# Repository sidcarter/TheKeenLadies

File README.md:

# Acheron TKL-SM-S-ATM32U4-MX-TH-WI (Codename "TheKeenLadies")

See [this page](https://gondolindrim.github.io/AcheronDocs/keenladies/intro.html) for the TheKeenLadies documentation.

## Supported layouts

Click [this link](http://www.keyboard-layout-editor.com/#/gists/6fcb43072b2efaa6a5129e3db566da86) for the KLE file for the TheKeenLadies PCB.

## Renders

Click at the images to zoom in.

Renders generated by the [tracespace.io](https://tracespace.io/view/) site.

## Copyright notice

This project is released under the Acheron Open-Hardware License V1.1. For the license, please refer to the LICENCE.md file.

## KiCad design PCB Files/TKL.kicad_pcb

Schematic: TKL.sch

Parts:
C1, C2, C3, C4, C5, C6, C7, C8, C9, C10, C11, C12, C13, C14, C15, C16, C17, C18, C19, C20, C21, C22, C23, C24, C25, C26, C27, C28, C29, C30, C31, C32, C33, C34, C35, C36, C37, C38, C39, C40, C41, C42, C43, C44, C45, C46, C47, C48, C49, C50, C51, C52, C53, C54, C55, C56, C57, C58, C59, C60, C61, C62, C63, C64, C102, C105: 100nF; C_0805_2012Metric
CB1: 1uF; C_0402_1005Metric
CB2, CB3, CB4, CB5, CB6: 100nF; C_0402_1005Metric
CF1: 1u; C_0805_2012Metric_Pad1.15x1.40mm_HandSolder
CRST1: 100nF; C_0402_1005Metric
CSH1: 100nF; C_0805_2012Metric_Pad1.15x1.40mm_HandSolder
CU1: 1uF; C_0402_1005Metric
CUSB1: 100nF; C_0402_1005Metric
CX1, CX2: 8.2pF; C_0402_1005Metric
D1, D2, D3, D4, D5, D6, D7, D8, D9, D10, D11, D12, D13, D14, D15, D16, D17, D18, D19, D20, D21, D22, D23, D24, D25, D26, D27, D28, D29, D30, D31, D32, D33, D34, D35, D36, D37, D38, D39, D40, D41, D42, D43, D44, D45, D46, D47, D48, D49, D50, D51, D52, D53, D54, D55, D56, D57, D58, D59, D60, D61, D62, D63, D64, D65, D66, D67, D68, D69, D70, D71, D72, D73, D74, D75, D76, D77, D78, D79, D80, D81, D82, D83, D84, D85, D86, D87, D88, D89, D90: 1N4148; D_SOD-123
DF1: RB060M-60TR; D_SOD-123
F1: Polyfuse; Fuse_1206_3216Metric
G1: TKL Logo; TKL_Logo_11x18mm_Plated
G2: Acheron Short Logo Plated; acheronShort_15.2x21mm_Plated
G3: Warning sign; warning_sign_3.6x3.2mm
J1: USB_C; TYPE-C-31-M-12
L1, L2, L3, L4, L5, L6, L7, L8, L9, L10, L11, L12, L13, L14, L15, L16, L17, L18, L19, L20, L21, L22, L23, L24, L25, L26, L27, L28, L29, L30, L31, L32, L33, L34, L35, L36, L37, L38, L39, L40, L41, L42, L43, L44, L45, L46, L47, L48, L49, L50, L51, L52, L53, L54, L55, L56, L57, L58, L59, L60, L61, L62, L63, L64, L102, L105: LED_BGRA; LED_RGB_SMD_6028_2.8x3.5mm_Round
R1, R2, R3, R4, R5, R6, R7, R8, R9, R10, R11, R12, R13, R14, R15, R16, R17, R18, R19, R20, R21, R22, R23, R24, R25, R26, R27, R28, R29, R30, R31, R32, R33, R34, R35, R36, R37, R38, R39, R40, R41, R42, R43, R44, R45, R46, R47, R48, R49, R50, R51, R52, R53, R54, R55, R56, R57, R58, R59, R60, R61, R62, R63, R64, R102, R105: 100R; R_0805_2012Metric
RCC1: 5.1k; R_SMD_1026
RD1, RD2, RD3, RD4, RD5, RD6, RD7, RD8, RD9, RD10, RD11, RD12, RD13, RD14, RD15, RD16, RD18, RD19, RD20, RD21, RD22, RD23, RD24, RD25, RD26, RD27, RD28, RD29, RD30, RD31, RD32, RD33, RD34, RD35, RD36, RD37, RD38, RD39, RD40, RD41, RD42, RD43, RD44, RD45, RD46, RD47, RD48, RD49, RD50, RD51, RD52, RD54, RD55, RD56, RD57, RD58, RD59, RD60, RD61, RD62, RD63, RD64, RD102, RD105: 33R; R_0805_2012Metric
RDM1: 22; R_0805_2012Metric
RDP1: 22; R_0805_2012Metric
RDR1, RDR2: 33R; R_0805_2012Metric
RF1: 10k; R_SMD_1026
RHWB1: 1k; R_SMD_1026
RRST1: 4.7k; R_0805_2012Metric
RRST2: 330R; R_0805_2012Metric
RSH1: 1M; R_SMD_1026
SW1: ESC; MX100
SW2: F1; MX100
SW3: F2; MX100
SW4: F3; MX100
SW5: F4; MX100
SW6: F5; MX100
SW7: F6; MX100
SW8: F7; MX100
SW9: F8; MX100
SW10: F9; MX100
SW11: F10; MX100
SW12: F11; MX100
SW13: F12; MX100
SW14: PRTSC; MX100
SW15: SCRLCK; MX100
SW16: PAUSE; MX100
SW17: GRV; MX100
SW18: 1; MX100
SW19: 2; MX100
SW20: 3; MX100
SW21: 4; MX100
SW22: 5; MX100
SW23: 6; MX100
SW24: 7; MX100
SW25: 8; MX100
SW26: 9; MX100
SW27: 0; MX100
SW28: HIFEN; MX100
SW29: PLUS; MX100
SW30: BCKSLSH; MX100
SW31, SW49: DEL; MX100
SW32: INS; MX100
SW33: HOME; MX100
SW34: PGUP; MX100
SW35: TAB; MX150
SW36: Q; MX100
SW37: W; MX100
SW38: E; MX100
SW39: R; MX100
SW40: T; MX100
SW41: Y; MX100
SW42: U; MX100
SW43: I; MX100
SW44: O; MX100
SW45: P; MX100
SW46: LBRACES; MX100
SW47: RBRACES; MX100
SW48: BKSP_150; MX150
SW50: END; MX100
SW51: PGDN; MX100
SW52: CAPS; MX175
SW53: A; MX100
SW54: S; MX100
SW55: D; MX100
SW56: F; MX100
SW57: G; MX100
SW58: H; MX100
SW59: J; MX100
SW60: K; MX100
SW61: L; MX100
SW62: :; MX100
SW63: QUOTE; MX100
SW64: ENTER; MX225
SW65: LSHFT; MX225
SW66: Z; MX100
SW67: X; MX100
SW68: C; MX100
SW69: V; MX100
SW70: B; MX100
SW71: N; MX100
SW72: M; MX100
SW73: <,; MX100
SW74: .>; MX100
SW75: /; MX100
SW76: RSHFT_275; MX275
SW77: UP; MX100
SW78: LCTRL_B1; MX125
SW79: LGUI_B1; MX125
SW80: LALT_B1; MX125
SW81: SPACE_B1; MX625R
SW82: RALT_B1; MX125
SW83: RGUI_B1; MX125
SW84: MENU_R1; MX125
SW85: RCTRL_R1; MX125
SW86: LEFT; MX100
SW87: DOWN; MX100
SW88: RIGHT; MX100
SW89: LCTRL_B2; MX150
SW90: LGUI_B2; MX100
SW91: LALT_B3; MX100
SW92: LALT_B2; MX150
SW93: LGUI_B3; MX125
SW94: LSPC_R3; MX225R
SW95: SPACE_B2; MX700R
SW96: RSPC_B3; MX275R
SW97: RGUI_R3; MX125
SW98: RALT_B2; MX150
SW99: RALT_R3; MX100
SW100: RGUI_R2; MX100
SW101: RCTRL_R2; MX150
SW102: STEPPED_CAPS; MX125
SW103: RSHFT_175; MX175
SW104: Fn; MX100
SW105: BKSP_2U; MX200
SW_RST1: SW_Push; smdPushBtn
U1, U2, U3, U4, U5, U6, U7, U8, U9, U10, U11, U12, U13, U14, U15, U16, U17, U18, U19, U20, U21, U22, U23, U24, U25, U26, U27, U28, U29, U30, U31, U32, U33, U34, U35, U36, U37, U38, U39, U40, U41, U42, U43, U44, U45, U46, U47, U48, U49, U50, U51, U52, U53, U54, U55, U56, U57, U58, U59, U60, U61, U62, U63, U64, U102, U105: WS2811M; MSOP-8-1EP_3x3mm_P0.65mm_EP1.68x1.88mm
U200: ATMEGA32U4; QFN-44-1EP_7x7mm_P0.5mm_EP5.2x5.2mm
U201: USBLC6-2SC6; SOT-23-6
X1: 16MHz; Crystal_SMD_2016-4Pin_2.0x1.6mm

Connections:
5V: CB1.2, CB2.1, CB3.2, CB4.2, CB5.1, CB6.1, CF1.2, DF1.1 (K), F1.1, L1.4 (A), L2.4 (A), L3.4 (A), L4.4 (A), L5.4 (A), L6.4 (A), L7.4 (A), L8.4 (A), L9.4 (A), L10.4 (A), L11.4 (A), L12.4 (A), L13.4 (A), L14.4 (A), L15.4 (A), L16.4 (A), L17.4 (A), L18.4 (A), L19.4 (A), L20.4 (A), L21.4 (A), L22.4 (A), L23.4 (A), L24.4 (A), L25.4 (A), L26.4 (A), L27.4 (A), L28.4 (A), L29.4 (A), L30.4 (A), L31.4 (A), L32.4 (A), L33.4 (A), L34.4 (A), L35.4 (A), L36.4 (A), L37.4 (A), L38.4 (A), L39.4 (A), L40.4 (A), L41.4 (A), L42.4 (A), L43.4 (A), L44.4 (A), L45.4 (A), L46.4 (A), L47.4 (A), L48.4 (A), L49.4 (A), L50.4 (A), L51.4 (A), L52.4 (A), L53.4 (A), L54.4 (A), L55.4 (A), L56.4 (A), L57.4 (A), L58.4 (A), L59.4 (A), L60.4 (A), L61.4 (A), L62.4 (A), L63.4 (A), L64.4 (A), L102.4 (A), L105.4 (A), R1.1, R2.1, R3.1, R4.1, R5.1, R6.1, R7.1, R8.1, R9.1, R10.1, R11.1, R12.1, R13.1, R14.1, R15.1, R16.1, R17.1, R18.1, R19.1, R20.1, R21.1, R22.1, R23.1, R24.1, R25.1, R26.1, R27.1, R28.1, R29.1, R30.1, R31.1, R32.1, R33.1, R34.1, R35.1, R36.1, R37.1, R38.1, R39.1, R40.1, R41.1, R42.1, R43.1, R44.1, R45.1, R46.1, R47.1, R48.1, R49.1, R50.1, R51.1, R52.1, R53.1, R54.1, R55.1, R56.1, R57.1, R58.1, R59.1, R60.1, R61.1, R62.1, R63.1, R64.1, R102.1, R105.1, RF1.2, RRST1.2, U200.2 (UVCC), U200.7 (VBUS), U200.14 (VCC), U200.24 (AVCC), U200.35 (GND), U200.42 (AREF), U200.44 (AVCC)
/RST: CRST1.2, RRST1.1, RRST2.2, U200.13 (~RESET~)
/SHIELD: CSH1.1, J1.S (SHIELD), RSH1.2
/XTAL1: CX2.1, U200.17 (XTAL1), X1.1
/XTAL2: CX1.1, U200.16 (XTAL2), X1.3
Col1: SW1.1 (Col), SW17.1 (Col), SW35.1 (Col), SW52.1 (Col), SW65.1 (Col), SW78.1 (Col), SW89.1 (Col), SW102.1 (Col)
Col2: SW18.1 (Col), SW36.1 (Col), SW53.1 (Col), SW66.1 (Col), SW79.1 (Col), SW90.1 (Col), SW91.1 (Col)
Col3: SW2.1 (Col), SW19.1 (Col), SW37.1 (Col), SW54.1 (Col), SW67.1 (Col), SW80.1 (Col), SW92.1 (Col), SW93.1 (Col)
Col4: SW3.1 (Col), SW20.1 (Col), SW38.1 (Col), SW55.1 (Col), SW68.1 (Col)
Col5: SW4.1 (Col), SW21.1 (Col), SW39.1 (Col), SW56.1 (Col), SW69.1 (Col), SW94.1 (Col)
Col6: SW5.1 (Col), SW22.1 (Col), SW40.1 (Col), SW57.1 (Col), SW70.1 (Col)
Col7: SW23.1 (Col), SW41.1 (Col), SW58.1 (Col), SW71.1 (Col), SW81.1 (Col), SW95.1 (Col), SW96.1 (Col)
Col8: SW6.1 (Col), SW24.1 (Col), SW42.1 (Col), SW59.1 (Col), SW72.1 (Col)
Col9: SW7.1 (Col), SW25.1 (Col), SW43.1 (Col), SW60.1 (Col), SW73.1 (Col)
Col10: SW8.1 (Col), SW26.1 (Col), SW44.1 (Col), SW61.1 (Col), SW74.1 (Col), SW82.1 (Col), SW97.1 (Col)
Col11: SW9.1 (Col), SW27.1 (Col), SW45.1 (Col), SW62.1 (Col), SW75.1 (Col), SW83.1 (Col), SW98.1 (Col), SW99.1 (Col)
Col12: SW10.1 (Col), SW28.1 (Col), SW46.1 (Col)
Col13: SW11.1 (Col), SW29.1 (Col), SW47.1 (Col), SW63.1 (Col), SW76.1 (Col), SW84.1 (Col), SW100.1 (Col), SW103.1 (Col)
Col14: SW12.1 (Col), SW30.1 (Col)
Col15: SW13.1 (Col), SW31.1 (Col), SW48.1 (Col), SW64.1 (Col), SW85.1 (Col), SW101.1 (Col), SW104.1 (Col), SW105.1 (Col)
Col16: SW14.1 (Col), SW32.1 (Col), SW49.1 (Col), SW86.1 (Col)
Col17: SW15.1 (Col), SW33.1 (Col), SW50.1 (Col), SW77.1 (Col), SW87.1 (Col)
Col18: SW16.1 (Col), SW34.1 (Col), SW51.1 (Col), SW88.1 (Col)
DBusN: J1.A7 (D-), J1.B7 (D-), U201.1 (IO1)
DBusP: J1.A6 (D+), J1.B6 (D+), U201.3 (IO2)
DN: RDM1.2, U200.3 (D-)
DP: RDP1.1, U200.4 (D+)
GND: C1.2, C2.2, C3.2, C4.2, C5.2, C6.2, C7.2, C8.2, C9.2, C10.2, C11.2, C12.2, C13.2, C14.2, C15.2, C16.2, C17.2, C18.2, C19.2, C20.2, C21.2, C22.2, C23.2, C24.2, C25.2, C26.2, C27.2, C28.2, C29.2, C30.2, C31.2, C32.2, C33.2, C34.2, C35.2, C36.2, C37.2, C38.2, C39.2, C40.2, C41.2, C42.2, C43.2, C44.2, C45.2, C46.2, C47.2, C48.2, C49.2, C50.2, C51.2, C52.2, C53.2, C54.2, C55.2, C56.2, C57.2, C58.2, C59.2, C60.2, C61.2, C62.2, C63.2, C64.2, C102.2, C105.2, CB1.1, CB2.2, CB3.1, CB4.1, CB5.2, CB6.2, CF1.1, CRST1.1, CSH1.2, CU1.2, CUSB1.2, CX1.2, CX2.2, DF1.2 (A), J1.A1 (GND), J1.B1 (GND), RCC1.2, RF1.1, RHWB1.1, RSH1.1, SW_RST1.1, U1.4 (GND), U1.9 (GND), U2.4 (GND), U2.9 (GND), U3.4 (GND), U3.9 (GND), U4.4 (GND), U4.9 (GND), U5.4 (GND), U5.9 (GND), U6.4 (GND), U6.9 (GND), U7.4 (GND), U7.9 (GND), U8.4 (GND), U8.9 (GND), U9.4 (GND), U9.9 (GND), U10.4 (GND), U10.9 (GND), U11.4 (GND), U11.9 (GND), U12.4 (GND), U12.9 (GND), U13.4 (GND), U13.9 (GND), U14.4 (GND), U14.9 (GND), U15.4 (GND), U15.9 (GND), U16.4 (GND), U16.9 (GND), U17.4 (GND), U17.9 (GND), U18.4 (GND), U18.9 (GND), U19.4 (GND), U19.9 (GND), U20.4 (GND), U20.9 (GND), U21.4 (GND), U21.9 (GND), U22.4 (GND), U22.9 (GND), U23.4 (GND), U23.9 (GND), U24.4 (GND), U24.9 (GND), U25.4 (GND), U25.9 (GND), U26.4 (GND), U26.9 (GND), U27.4 (GND), U27.9 (GND), U28.4 (GND), U28.9 (GND), U29.4 (GND), U29.9 (GND), U30.4 (GND), U30.9 (GND), U31.4 (GND), U31.9 (GND), U32.4 (GND), U32.9 (GND), U33.4 (GND), U33.9 (GND), U34.4 (GND), U34.9 (GND), U35.4 (GND), U35.9 (GND), U36.4 (GND), U36.9 (GND), U37.4 (GND), U37.9 (GND), U38.4 (GND), U38.9 (GND), U39.4 (GND), U39.9 (GND), U40.4 (GND), U40.9 (GND), U41.4 (GND), U41.9 (GND), U42.4 (GND), U42.9 (GND), U43.4 (GND), U43.9 (GND), U44.4 (GND), U44.9 (GND), U45.4 (GND), U45.9 (GND), U46.4 (GND), U46.9 (GND), U47.4 (GND), U47.9 (GND), U48.4 (GND), U48.9 (GND), U49.4 (GND), U49.9 (GND), U50.4 (GND), U50.9 (GND), U51.4 (GND), U51.9 (GND), U52.4 (GND), U52.9 (GND), U53.4 (GND), U53.9 (GND), U54.4 (GND), U54.9 (GND), U55.4 (GND), U55.9 (GND), U56.4 (GND), U56.9 (GND), U57.4 (GND), U57.9 (GND), U58.4 (GND), U58.9 (GND), U59.4 (GND), U59.9 (GND), U60.4 (GND), U60.9 (GND), U61.4 (GND), U61.9 (GND), U62.4 (GND), U62.9 (GND), U63.4 (GND), U63.9 (GND), U64.4 (GND), U64.9 (GND), U102.4 (GND), U102.9 (GND), U105.4 (GND), U105.9 (GND), U200.5 (UGND), U200.15 (GND), U200.23 (GND), U200.34 (VCC), U200.43 (GND), U201.2 (GND), X1.2, X1.4
L1: D78.2 (A), SW78.2 (Row), SW89.2 (Row)
L2: D79.2 (A), SW79.2 (Row), SW90.2 (Row), SW91.2 (Row)
L3: D80.2 (A), SW80.2 (Row), SW92.2 (Row), SW93.2 (Row)
L4: D81.2 (A), SW81.2 (Row), SW95.2 (Row), SW96.2 (Row)
L5: D82.2 (A), SW82.2 (Row), SW97.2 (Row)
L6: D83.2 (A), SW83.2 (Row), SW98.2 (Row), SW99.2 (Row)
L7: D84.2 (A), SW84.2 (Row), SW100.2 (Row)
L8: D85.2 (A), SW85.2 (Row), SW101.2 (Row)
unnamed: C1.1, R1.2, U1.8 (VDD)
unnamed: C2.1, R2.2, U2.8 (VDD)
unnamed: C3.1, R3.2, U3.8 (VDD)
unnamed: C4.1, R4.2, U4.8 (VDD)
unnamed: C5.1, R5.2, U5.8 (VDD)
unnamed: C6.1, R6.2, U6.8 (VDD)
unnamed: C7.1, R7.2, U7.8 (VDD)
unnamed: C8.1, R8.2, U8.8 (VDD)
unnamed: C9.1, R9.2, U9.8 (VDD)
unnamed: C10.1, R10.2, U10.8 (VDD)
unnamed: C11.1, R11.2, U11.8 (VDD)
unnamed: C12.1, R12.2, U12.8 (VDD)
unnamed: C13.1, R13.2, U13.8 (VDD)
unnamed: C14.1, R14.2, U14.8 (VDD)
unnamed: C15.1, R15.2, U15.8 (VDD)
unnamed: C16.1, R16.2, U16.8 (VDD)
unnamed: C17.1, R17.2, U17.8 (VDD)
unnamed: C18.1, R18.2, U18.8 (VDD)
unnamed: C19.1, R19.2, U19.8 (VDD)
unnamed: C20.1, R20.2, U20.8 (VDD)
unnamed: C21.1, R21.2, U21.8 (VDD)
unnamed: C22.1, R22.2, U22.8 (VDD)
unnamed: C23.1, R23.2, U23.8 (VDD)
unnamed: C24.1, R24.2, U24.8 (VDD)
unnamed: C25.1, R25.2, U25.8 (VDD)
unnamed: C26.1, R26.2, U26.8 (VDD)
unnamed: C27.1, R27.2, U27.8 (VDD)
unnamed: C28.1, R28.2, U28.8 (VDD)
unnamed: C29.1, R29.2, U29.8 (VDD)
unnamed: C30.1, R30.2, U30.8 (VDD)
unnamed: C31.1, R31.2, U31.8 (VDD)
unnamed: C32.1, R32.2, U32.8 (VDD)
unnamed: C33.1, R33.2, U33.8 (VDD)
unnamed: C34.1, R34.2, U34.8 (VDD)
unnamed: C35.1, R35.2, U35.8 (VDD)
unnamed: C36.1, R36.2, U36.8 (VDD)
unnamed: C37.1, R37.2, U37.8 (VDD)
unnamed: C38.1, R38.2, U38.8 (VDD)
unnamed: C39.1, R39.2, U39.8 (VDD)
unnamed: C40.1, R40.2, U40.8 (VDD)
unnamed: C41.1, R41.2, U41.8 (VDD)
unnamed: C42.1, R42.2, U42.8 (VDD)
unnamed: C43.1, R43.2, U43.8 (VDD)
unnamed: C44.1, R44.2, U44.8 (VDD)
unnamed: C45.1, R45.2, U45.8 (VDD)
unnamed: C46.1, R46.2, U46.8 (VDD)
unnamed: C47.1, R47.2, U47.8 (VDD)
unnamed: C48.1, R48.2, U48.8 (VDD)
unnamed: C49.1, R49.2, U49.8 (VDD)
unnamed: C50.1, R50.2, U50.8 (VDD)
unnamed: C51.1, R51.2, U51.8 (VDD)
unnamed: C52.1, R52.2, U52.8 (VDD)
unnamed: C53.1, R53.2, U53.8 (VDD)
unnamed: C54.1, R54.2, U54.8 (VDD)
unnamed: C55.1, R55.2, U55.8 (VDD)
unnamed: C56.1, R56.2, U56.8 (VDD)
unnamed: C57.1, R57.2, U57.8 (VDD)
unnamed: C58.1, R58.2, U58.8 (VDD)
unnamed: C59.1, R59.2, U59.8 (VDD)
unnamed: C60.1, R60.2, U60.8 (VDD)
unnamed: C61.1, R61.2, U61.8 (VDD)
unnamed: C62.1, R62.2, U62.8 (VDD)
unnamed: C63.1, R63.2, U63.8 (VDD)
unnamed: C64.1, R64.2, U64.8 (VDD)
unnamed: C102.1, R102.2, U102.8 (VDD)
unnamed: C105.1, R105.2, U105.8 (VDD)
unnamed: CU1.1, U200.6 (UCAP)
unnamed: D1.2 (A), SW1.2 (Row)
unnamed: D2.2 (A), SW2.2 (Row)
unnamed: D3.2 (A), SW3.2 (Row)
unnamed: D4.2 (A), SW4.2 (Row)
unnamed: D5.2 (A), SW5.2 (Row)
unnamed: D6.2 (A), SW6.2 (Row)
unnamed: D7.2 (A), SW7.2 (Row)
unnamed: D8.2 (A), SW8.2 (Row)
unnamed: D9.2 (A), SW9.2 (Row)
unnamed: D10.2 (A), SW10.2 (Row)
unnamed: D11.2 (A), SW11.2 (Row)
unnamed: D12.2 (A), SW12.2 (Row)
unnamed: D13.2 (A), SW13.2 (Row)
unnamed: D14.2 (A), SW14.2 (Row)
unnamed: D15.2 (A), SW15.2 (Row)
unnamed: D16.2 (A), SW16.2 (Row)
unnamed: D17.2 (A), SW17.2 (Row)
unnamed: D18.2 (A), SW18.2 (Row)
unnamed: D19.2 (A), SW19.2 (Row)
unnamed: D20.2 (A), SW20.2 (Row)
unnamed: D21.2 (A), SW21.2 (Row)
unnamed: D22.2 (A), SW22.2 (Row)
unnamed: D23.2 (A), SW23.2 (Row)
unnamed: D24.2 (A), SW24.2 (Row)
unnamed: D25.2 (A), SW25.2 (Row)
unnamed: D26.2 (A), SW26.2 (Row)
unnamed: D27.2 (A), SW27.2 (Row)
unnamed: D28.2 (A), SW28.2 (Row)
unnamed: D29.2 (A), SW29.2 (Row)
unnamed: D30.2 (A), SW30.2 (Row)
unnamed: D31.2 (A), SW31.2 (Row), SW105.2 (Row)
unnamed: D32.2 (A), SW32.2 (Row)
unnamed: D33.2 (A), SW33.2 (Row)
unnamed: D34.2 (A), SW34.2 (Row)
unnamed: D35.2 (A), SW35.2 (Row)
unnamed: D36.2 (A), SW36.2 (Row)
unnamed: D37.2 (A), SW37.2 (Row)
unnamed: D38.2 (A), SW38.2 (Row)
unnamed: D39.2 (A), SW39.2 (Row)
unnamed: D40.2 (A), SW40.2 (Row)
unnamed: D41.2 (A), SW41.2 (Row)
unnamed 144: D42.2 (A), SW42.2 (Row); also elsewhere on the board
unnamed: D43.2 (A), SW43.2 (Row)
unnamed: D44.2 (A), SW44.2 (Row)
unnamed: D45.2 (A), SW45.2 (Row)
unnamed: D46.2 (A), SW46.2 (Row)
unnamed: D47.2 (A), SW47.2 (Row)
unnamed: D48.2 (A), SW48.2 (Row)
unnamed: D49.2 (A), SW49.2 (Row)
unnamed: D50.2 (A), SW50.2 (Row)
unnamed: D51.2 (A), SW51.2 (Row)
unnamed: D52.2 (A), SW52.2 (Row), SW102.2 (Row)
unnamed: D53.2 (A), SW53.2 (Row)
unnamed: D54.2 (A), SW54.2 (Row)
unnamed: D55.2 (A), SW55.2 (Row)
unnamed: D56.2 (A), SW56.2 (Row)
unnamed: D57.2 (A), SW57.2 (Row)
unnamed: D58.2 (A), SW58.2 (Row)
unnamed: D59.2 (A), SW59.2 (Row)
unnamed: D60.2 (A), SW60.2 (Row)
unnamed: D61.2 (A), SW61.2 (Row)
unnamed: D62.2 (A), SW62.2 (Row)
unnamed: D63.2 (A), SW63.2 (Row)
unnamed: D64.2 (A), SW64.2 (Row)
unnamed: D65.2 (A), SW65.2 (Row)
unnamed: D66.2 (A), SW66.2 (Row)
unnamed: D67.2 (A), SW67.2 (Row)
unnamed: D68.2 (A), SW68.2 (Row)
unnamed: D69.2 (A), SW69.2 (Row)
unnamed: D70.2 (A), SW70.2 (Row)
unnamed: D71.2 (A), SW71.2 (Row)
unnamed: D72.2 (A), SW72.2 (Row)
unnamed: D73.2 (A), SW73.2 (Row)
unnamed: D74.2 (A), SW74.2 (Row)
unnamed: D75.2 (A), SW75.2 (Row)
unnamed: D76.2 (A), SW76.2 (Row), SW103.2 (Row)
unnamed: D77.2 (A), SW77.2 (Row)
unnamed: D86.2 (A), SW86.2 (Row)
unnamed: D87.2 (A), SW87.2 (Row)
unnamed: D88.2 (A), SW88.2 (Row)
unnamed: D89.2 (A), SW94.2 (Row)
unnamed: D90.2 (A), SW104.2 (Row)
unnamed: J1.A5 (CC1), J1.B5 (CC2), RCC1.1
unnamed: L1.1 (BK), U1.3 (OUTB)
unnamed: L1.2 (GK), U1.2 (OUTG)
unnamed: L1.3 (RK), U1.1 (OUTR)
unnamed: L2.1 (BK), U2.3 (OUTB)
unnamed: L2.2 (GK), U2.2 (OUTG)
unnamed: L2.3 (RK), U2.1 (OUTR)
unnamed: L3.1 (BK), U3.3 (OUTB)
unnamed: L3.2 (GK), U3.2 (OUTG)
unnamed: L3.3 (RK), U3.1 (OUTR)
unnamed: L4.1 (BK), U4.3 (OUTB)
unnamed: L4.2 (GK), U4.2 (OUTG)
unnamed: L4.3 (RK), U4.1 (OUTR)
unnamed: L5.1 (BK), U5.3 (OUTB)
unnamed: L5.2 (GK), U5.2 (OUTG)
unnamed: L5.3 (RK), U5.1 (OUTR)
unnamed: L6.1 (BK), U6.3 (OUTB)
unnamed: L6.2 (GK), U6.2 (OUTG)
unnamed: L6.3 (RK), U6.1 (OUTR)
unnamed: L7.1 (BK), U7.3 (OUTB)
unnamed: L7.2 (GK), U7.2 (OUTG)
unnamed: L7.3 (RK), U7.1 (OUTR)
unnamed: L8.1 (BK), U8.3 (OUTB)
unnamed: L8.2 (GK), U8.2 (OUTG)
unnamed: L8.3 (RK), U8.1 (OUTR)
unnamed: L9.1 (BK), U9.3 (OUTB)
unnamed: L9.2 (GK), U9.2 (OUTG)
unnamed: L9.3 (RK), U9.1 (OUTR)
unnamed: L10.1 (BK), U10.3 (OUTB)
unnamed: L10.2 (GK), U10.2 (OUTG)
unnamed: L10.3 (RK), U10.1 (OUTR)
unnamed: L11.1 (BK), U11.3 (OUTB)
unnamed: L11.2 (GK), U11.2 (OUTG)
unnamed: L11.3 (RK), U11.1 (OUTR)
unnamed: L12.1 (BK), U12.3 (OUTB)
unnamed: L12.2 (GK), U12.2 (OUTG)
unnamed: L12.3 (RK), U12.1 (OUTR)
unnamed: L13.1 (BK), U13.3 (OUTB)
unnamed: L13.2 (GK), U13.2 (OUTG)
unnamed: L13.3 (RK), U13.1 (OUTR)
unnamed: L14.1 (BK), U14.3 (OUTB)
unnamed: L14.2 (GK), U14.2 (OUTG)
unnamed: L14.3 (RK), U14.1 (OUTR)
unnamed: L15.1 (BK), U15.3 (OUTB)
unnamed: L15.2 (GK), U15.2 (OUTG)
unnamed: L15.3 (RK), U15.1 (OUTR)
unnamed: L16.1 (BK), U16.3 (OUTB)
unnamed: L16.2 (GK), U16.2 (OUTG)
unnamed: L16.3 (RK), U16.1 (OUTR)
unnamed: L17.1 (BK), U17.3 (OUTB)
unnamed: L17.2 (GK), U17.2 (OUTG)
unnamed: L17.3 (RK), U17.1 (OUTR)
unnamed: L18.1 (BK), U18.3 (OUTB)
unnamed: L18.2 (GK), U18.2 (OUTG)
unnamed: L18.3 (RK), U18.1 (OUTR)
unnamed: L19.1 (BK), U19.3 (OUTB)
unnamed: L19.2 (GK), U19.2 (OUTG)
unnamed: L19.3 (RK), U19.1 (OUTR)
unnamed: L20.1 (BK), U20.3 (OUTB)
unnamed: L20.2 (GK), U20.2 (OUTG)
unnamed: L20.3 (RK), U20.1 (OUTR)
unnamed: L21.1 (BK), U21.3 (OUTB)
unnamed: L21.2 (GK), U21.2 (OUTG)
unnamed: L21.3 (RK), U21.1 (OUTR)
unnamed: L22.1 (BK), U22.3 (OUTB)
unnamed: L22.2 (GK), U22.2 (OUTG)
unnamed: L22.3 (RK), U22.1 (OUTR)
unnamed: L23.1 (BK), U23.3 (OUTB)
unnamed: L23.2 (GK), U23.2 (OUTG)
unnamed: L23.3 (RK), U23.1 (OUTR)
unnamed: L24.1 (BK), U24.3 (OUTB)
unnamed: L24.2 (GK), U24.2 (OUTG)
unnamed: L24.3 (RK), U24.1 (OUTR)
unnamed: L25.1 (BK), U25.3 (OUTB)
unnamed: L25.2 (GK), U25.2 (OUTG)
unnamed: L25.3 (RK), U25.1 (OUTR)
unnamed: L26.1 (BK), U26.3 (OUTB)
unnamed: L26.2 (GK), U26.2 (OUTG)
unnamed: L26.3 (RK), U26.1 (OUTR)
unnamed: L27.1 (BK), U27.3 (OUTB)
unnamed: L27.2 (GK), U27.2 (OUTG)
unnamed: L27.3 (RK), U27.1 (OUTR)
unnamed: L28.1 (BK), U28.3 (OUTB)
unnamed: L28.2 (GK), U28.2 (OUTG)
unnamed: L28.3 (RK), U28.1 (OUTR)
unnamed: L29.1 (BK), U29.3 (OUTB)
unnamed: L29.2 (GK), U29.2 (OUTG)
unnamed: L29.3 (RK), U29.1 (OUTR)
unnamed: L30.1 (BK), U30.3 (OUTB)
unnamed: L30.2 (GK), U30.2 (OUTG)
unnamed: L30.3 (RK), U30.1 (OUTR)
unnamed: L31.1 (BK), U31.3 (OUTB)
unnamed: L31.2 (GK), U31.2 (OUTG)
unnamed: L31.3 (RK), U31.1 (OUTR)
unnamed: L32.1 (BK), U32.3 (OUTB)
unnamed: L32.2 (GK), U32.2 (OUTG)
unnamed: L32.3 (RK), U32.1 (OUTR)
unnamed: L33.1 (BK), U33.3 (OUTB)
unnamed: L33.2 (GK), U33.2 (OUTG)
unnamed: L33.3 (RK), U33.1 (OUTR)
unnamed: L34.1 (BK), U34.3 (OUTB)
unnamed: L34.2 (GK), U34.2 (OUTG)
unnamed: L34.3 (RK), U34.1 (OUTR)
unnamed: L35.1 (BK), U35.3 (OUTB)
unnamed: L35.2 (GK), U35.2 (OUTG)
unnamed: L35.3 (RK), U35.1 (OUTR)
unnamed: L36.1 (BK), U36.3 (OUTB)
unnamed: L36.2 (GK), U36.2 (OUTG)
unnamed: L36.3 (RK), U36.1 (OUTR)
unnamed: L37.1 (BK), U37.3 (OUTB)
unnamed: L37.2 (GK), U37.2 (OUTG)
unnamed: L37.3 (RK), U37.1 (OUTR)
unnamed: L38.1 (BK), U38.3 (OUTB)
unnamed: L38.2 (GK), U38.2 (OUTG)
unnamed: L38.3 (RK), U38.1 (OUTR)
unnamed: L39.1 (BK), U39.3 (OUTB)
unnamed: L39.2 (GK), U39.2 (OUTG)
unnamed: L39.3 (RK), U39.1 (OUTR)
unnamed: L40.1 (BK), U40.3 (OUTB)
unnamed: L40.2 (GK), U40.2 (OUTG)
unnamed: L40.3 (RK), U40.1 (OUTR)
unnamed: L41.1 (BK), U41.3 (OUTB)
unnamed: L41.2 (GK), U41.2 (OUTG)
unnamed: L41.3 (RK), U41.1 (OUTR)
unnamed: L42.1 (BK), U42.3 (OUTB)
unnamed: L42.2 (GK), U42.2 (OUTG)
unnamed: L42.3 (RK), U42.1 (OUTR)
unnamed: L43.1 (BK), U43.3 (OUTB)
unnamed: L43.2 (GK), U43.2 (OUTG)
unnamed: L43.3 (RK), U43.1 (OUTR)
unnamed: L44.1 (BK), U44.3 (OUTB)
unnamed: L44.2 (GK), U44.2 (OUTG)
unnamed: L44.3 (RK), U44.1 (OUTR)
unnamed: L45.1 (BK), U45.3 (OUTB)
unnamed: L45.2 (GK), U45.2 (OUTG)
unnamed: L45.3 (RK), U45.1 (OUTR)
unnamed: L46.1 (BK), U46.3 (OUTB)
unnamed: L46.2 (GK), U46.2 (OUTG)
unnamed: L46.3 (RK), U46.1 (OUTR)
unnamed: L47.1 (BK), U47.3 (OUTB)
unnamed: L47.2 (GK), U47.2 (OUTG)
unnamed: L47.3 (RK), U47.1 (OUTR)
unnamed: L48.1 (BK), U48.3 (OUTB)
unnamed: L48.2 (GK), U48.2 (OUTG)
unnamed: L48.3 (RK), U48.1 (OUTR)
unnamed: L49.1 (BK), U49.3 (OUTB)
unnamed: L49.2 (GK), U49.2 (OUTG)
unnamed: L49.3 (RK), U49.1 (OUTR)
unnamed: L50.1 (BK), U50.3 (OUTB)
unnamed: L50.2 (GK), U50.2 (OUTG)
unnamed: L50.3 (RK), U50.1 (OUTR)
unnamed: L51.1 (BK), U51.3 (OUTB)
unnamed: L51.2 (GK), U51.2 (OUTG)
unnamed: L51.3 (RK), U51.1 (OUTR)
unnamed: L52.1 (BK), U52.3 (OUTB)
unnamed: L52.2 (GK), U52.2 (OUTG)
unnamed: L52.3 (RK), U52.1 (OUTR)
unnamed: L53.1 (BK), U53.3 (OUTB)
unnamed: L53.2 (GK), U53.2 (OUTG)
unnamed: L53.3 (RK), U53.1 (OUTR)
unnamed: L54.1 (BK), U54.3 (OUTB)
unnamed: L54.2 (GK), U54.2 (OUTG)
unnamed: L54.3 (RK), U54.1 (OUTR)
unnamed: L55.1 (BK), U55.3 (OUTB)
unnamed: L55.2 (GK), U55.2 (OUTG)
unnamed: L55.3 (RK), U55.1 (OUTR)
unnamed: L56.1 (BK), U56.3 (OUTB)
unnamed: L56.2 (GK), U56.2 (OUTG)
unnamed: L56.3 (RK), U56.1 (OUTR)
unnamed: L57.1 (BK), U57.3 (OUTB)
unnamed: L57.2 (GK), U57.2 (OUTG)
unnamed: L57.3 (RK), U57.1 (OUTR)
unnamed: L58.1 (BK), U58.3 (OUTB)
unnamed: L58.2 (GK), U58.2 (OUTG)
unnamed: L58.3 (RK), U58.1 (OUTR)
unnamed: L59.1 (BK), U59.3 (OUTB)
unnamed: L59.2 (GK), U59.2 (OUTG)
unnamed: L59.3 (RK), U59.1 (OUTR)
unnamed: L60.1 (BK), U60.3 (OUTB)
unnamed: L60.2 (GK), U60.2 (OUTG)
unnamed: L60.3 (RK), U60.1 (OUTR)
unnamed: L61.1 (BK), U61.3 (OUTB)
unnamed: L61.2 (GK), U61.2 (OUTG)
unnamed: L61.3 (RK), U61.1 (OUTR)
unnamed: L62.1 (BK), U62.3 (OUTB)
unnamed: L62.2 (GK), U62.2 (OUTG)
unnamed: L62.3 (RK), U62.1 (OUTR)
unnamed: L63.1 (BK), U63.3 (OUTB)
unnamed: L63.2 (GK), U63.2 (OUTG)
unnamed: L63.3 (RK), U63.1 (OUTR)
unnamed: L64.1 (BK), U64.3 (OUTB)
unnamed: L64.2 (GK), U64.2 (OUTG)
unnamed: L64.3 (RK), U64.1 (OUTR)
unnamed: L102.1 (BK), U102.3 (OUTB)
unnamed: L102.2 (GK), U102.2 (OUTG)
unnamed: L102.3 (RK), U102.1 (OUTR)
unnamed: L105.1 (BK), U105.3 (OUTB)
unnamed: L105.2 (GK), U105.2 (OUTG)
unnamed: L105.3 (RK), U105.1 (OUTR)
unnamed: RD1.1, U1.6 (DIN)
unnamed: RD2.1, U2.6 (DIN)
unnamed: RD2.2, U1.5 (DO)
unnamed: RD3.1, U3.6 (DIN)
unnamed: RD3.2, U2.5 (DO)
unnamed: RD4.1, U4.6 (DIN)
unnamed: RD4.2, U3.5 (DO)
unnamed: RD5.1, U5.6 (DIN)
unnamed: RD5.2, U4.5 (DO)
unnamed: RD6.1, U6.6 (DIN)
unnamed: RD6.2, U5.5 (DO)
unnamed: RD7.1, U7.6 (DIN)
unnamed: RD7.2, U6.5 (DO)
unnamed: RD8.1, U8.6 (DIN)
unnamed: RD8.2, U7.5 (DO)
unnamed: RD9.1, U9.6 (DIN)
unnamed: RD9.2, U8.5 (DO)
unnamed: RD10.1, U10.6 (DIN)
unnamed: RD10.2, U9.5 (DO)
unnamed: RD11.1, U11.6 (DIN)
unnamed: RD11.2, U10.5 (DO)
unnamed: RD12.1, U12.6 (DIN)
unnamed: RD12.2, U11.5 (DO)
unnamed: RD13.1, U13.6 (DIN)
unnamed: RD13.2, U12.5 (DO)
unnamed: RD14.1, U14.6 (DIN)
unnamed: RD14.2, U13.5 (DO)
unnamed: RD15.1, U15.6 (DIN)
unnamed: RD15.2, U14.5 (DO)
unnamed: RD16.1, U16.6 (DIN)
unnamed: RD16.2, U15.5 (DO)
unnamed: RD18.1, U17.6 (DIN)
unnamed: RD18.2, U18.5 (DO)
unnamed: RD19.1, U18.6 (DIN)
unnamed: RD19.2, U19.5 (DO)
unnamed: RD20.1, U19.6 (DIN)
unnamed: RD20.2, U20.5 (DO)
unnamed: RD21.1, U20.6 (DIN)
unnamed: RD21.2, U21.5 (DO)
unnamed: RD22.1, U21.6 (DIN)
unnamed: RD22.2, U22.5 (DO)
unnamed: RD23.1, U22.6 (DIN)
unnamed: RD23.2, U23.5 (DO)
unnamed: RD24.1, U23.6 (DIN)
unnamed: RD24.2, U24.5 (DO)
unnamed: RD25.1, U24.6 (DIN)
unnamed: RD25.2, U25.5 (DO)
unnamed: RD26.1, U25.6 (DIN)
unnamed: RD26.2, U26.5 (DO)
unnamed: RD27.1, U26.6 (DIN)
unnamed: RD27.2, U27.5 (DO)
unnamed: RD28.1, U27.6 (DIN)
unnamed: RD28.2, U28.5 (DO)
unnamed: RD29.1, U28.6 (DIN)
unnamed: RD29.2, U29.5 (DO)
unnamed: RD30.1, U29.6 (DIN)
unnamed: RD30.2, U30.5 (DO)
unnamed: RD31.1, U105.6 (DIN)
unnamed: RD31.2, U31.5 (DO)
unnamed: RD32.1, U31.6 (DIN)
unnamed: RD32.2, U32.5 (DO)
unnamed: RD33.1, U32.6 (DIN)
unnamed: RD33.2, U33.5 (DO)
unnamed: RD34.1, U33.6 (DIN)
unnamed: RD34.2, U34.5 (DO)
unnamed: RD35.1, U35.6 (DIN)
unnamed: RD35.2, U17.5 (DO)
unnamed: RD36.1, U36.6 (DIN)
unnamed: RD36.2, U35.5 (DO)
unnamed: RD37.1, U37.6 (DIN)
unnamed: RD37.2, U36.5 (DO)
unnamed: RD38.1, U38.6 (DIN)
unnamed: RD38.2, U37.5 (DO)
unnamed: RD39.1, U39.6 (DIN)
unnamed: RD39.2, U38.5 (DO)
unnamed: RD40.1, U40.6 (DIN)
unnamed: RD40.2, U39.5 (DO)
unnamed: RD41.1, U41.6 (DIN)
unnamed: RD41.2, U40.5 (DO)
unnamed: RD42.1, U42.6 (DIN)
unnamed: RD42.2, U41.5 (DO)
unnamed: RD43.1, U43.6 (DIN)
unnamed: RD43.2, U42.5 (DO)
unnamed: RD44.1, U44.6 (DIN)
unnamed: RD44.2, U43.5 (DO)
unnamed: RD45.1, U45.6 (DIN)
unnamed: RD45.2, U44.5 (DO)
unnamed: RD46.1, U46.6 (DIN)
unnamed: RD46.2, U45.5 (DO)
unnamed: RD47.1, U47.6 (DIN)
unnamed: RD47.2, U46.5 (DO)
unnamed: RD48.1, U48.6 (DIN)
unnamed: RD48.2, U47.5 (DO)
unnamed: RD49.1, U49.6 (DIN)
unnamed: RD49.2, U48.5 (DO)
unnamed: RD50.1, U50.6 (DIN)
unnamed: RD50.2, U49.5 (DO)
unnamed: RD51.1, U51.6 (DIN)
unnamed: RD51.2, U50.5 (DO)
unnamed: RD52.1, U102.5 (DO)
unnamed: RD52.2, U52.6 (DIN)
unnamed: RD54.1, U53.6 (DIN)
unnamed: RD54.2, U54.5 (DO)
unnamed: RD55.1, U54.6 (DIN)
unnamed: RD55.2, U55.5 (DO)
unnamed: RD56.1, U55.6 (DIN)
unnamed: RD56.2, U56.5 (DO)
unnamed: RD57.1, U56.6 (DIN)
unnamed: RD57.2, U57.5 (DO)
unnamed: RD58.1, U57.6 (DIN)
unnamed: RD58.2, U58.5 (DO)
unnamed: RD59.1, U58.6 (DIN)
unnamed: RD59.2, U59.5 (DO)
unnamed: RD60.1, U59.6 (DIN)
unnamed: RD60.2, U60.5 (DO)
unnamed: RD61.1, U60.6 (DIN)
unnamed: RD61.2, U61.5 (DO)
unnamed: RD62.1, U61.6 (DIN)
unnamed: RD62.2, U62.5 (DO)
unnamed: RD63.1, U62.6 (DIN)
unnamed: RD63.2, U63.5 (DO)
unnamed: RD64.1, U63.6 (DIN)
unnamed: RD64.2, U64.5 (DO)
unnamed: RD102.1, U102.6 (DIN)
unnamed: RD102.2, U53.5 (DO)
unnamed: RD105.1, U30.6 (DIN)
unnamed: RD105.2, U105.5 (DO)
unnamed: RDM1.1, U201.6 (IO1)
unnamed: RDP1.2, U201.4 (IO2)
unnamed: RDR1.1, U34.6 (DIN)
unnamed: RDR1.2, U16.5 (DO)
unnamed: RDR2.1, U64.6 (DIN)
unnamed: RDR2.2, U51.5 (DO)
unnamed: RHWB1.2, U200.33 (~HWB~/PE2)
unnamed: RRST2.1, SW_RST1.2
RGB_DIN: RD1.2, U200.27 (ADC10/T0/PD7)
Row1: D1.1 (K), D2.1 (K), D3.1 (K), D4.1 (K), D5.1 (K), D6.1 (K), D7.1 (K), D8.1 (K), D9.1 (K), D10.1 (K), D11.1 (K), D12.1 (K), D13.1 (K), D14.1 (K), D15.1 (K), D16.1 (K)
Row2: D17.1 (K), D18.1 (K), D19.1 (K), D20.1 (K), D21.1 (K), D22.1 (K), D23.1 (K), D24.1 (K), D25.1 (K), D26.1 (K), D27.1 (K), D28.1 (K), D29.1 (K), D30.1 (K), D31.1 (K), D32.1 (K), D33.1 (K), D34.1 (K)
Row3: D35.1 (K), D36.1 (K), D37.1 (K), D38.1 (K), D39.1 (K), D40.1 (K), D41.1 (K), D42.1 (K), D43.1 (K), D44.1 (K), D45.1 (K), D46.1 (K), D47.1 (K), D48.1 (K), D49.1 (K), D50.1 (K), D51.1 (K); also elsewhere on the board
Row4: D52.1 (K), D53.1 (K), D54.1 (K), D55.1 (K), D56.1 (K), D57.1 (K), D58.1 (K), D59.1 (K), D60.1 (K), D61.1 (K), D62.1 (K), D63.1 (K), D64.1 (K)
Row5: D65.1 (K), D66.1 (K), D67.1 (K), D68.1 (K), D69.1 (K), D70.1 (K), D71.1 (K), D72.1 (K), D74.1 (K), D75.1 (K), D76.1 (K), D77.1 (K), D90.1 (K)
Row6: D78.1 (K), D79.1 (K), D80.1 (K), D81.1 (K), D82.1 (K), D83.1 (K), D84.1 (K), D85.1 (K), D86.1 (K), D87.1 (K), D88.1 (K), D89.1 (K)
VBUS: CUSB1.1, F1.2, J1.A4 (VBUS), J1.B4 (VBUS), U201.5 (VBUS)

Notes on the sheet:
Decoupling or bypass capacitors. The AN2519 [2] indicates that the typical decoupling capacitor values are 100nF for analog voltage. It also recomends that the main VCC voltage be decoupled, but does not ecommend a value for this. The value used was 1uF.
CU1: this is the UCAP pin capacitor. The MCU datasheet [1] specifies that this pin should be connected to an external 1uF capacitor.
CBx capacitors:
CU1
The reset network added was taken directly from Application Note [2]. See section 3 for details.
RESET NETWORK
Crystal load capacitors. Thedatasheet [3] recommends a 8pF value. The 8.2pF value was used because it was more commonly found.
CX1/2 capacitors:
https://www.ndk.com/images/products/catalog/c_NX5032GC-STD-CSK-6_e.pdf
[3] NX5032GC 16MHz crystal datasheet
http://ww1.microchip.com/downloads/en/AppNotes/AN2519-AVR-Microcontroller-Hardware-Design-Considerations-00002519B.pdf
[2] AN2519 Application Note: AVR® Microcontroller Hardware Design Considerations
http://ww1.microchip.com/downloads/en/DeviceDoc/Atmel-7766-8-bit-AVR-ATmega16U4-32U4_Datasheet.pdf
[1] ATMEGA32U4 datasheet
[4] AN232B-06 Application Note
https://www.ftdichip.com/Support/Documents/AppNotes/AN232B-06_11.pdf
RHWB1
Datasheet [1] recommends that the HWB pin be connected to GNd through a 1k resistor.
[5] USBLC6-2 Datasheet
https://www.st.com/resource/en/datasheet/usblc6-2.pdf
REFERENCES
CSH1 and RSH1
In order to offer a low-impedance, low-inductance path to EMI and ESD, reference [4] recommends that the USB shield and ground pin be connected through a net consisting of a capacitor ranging between 10nF and 470nF and a high value resistor.
Reference [5] recommends that this capacitor be attached for decoupling
CUSB1

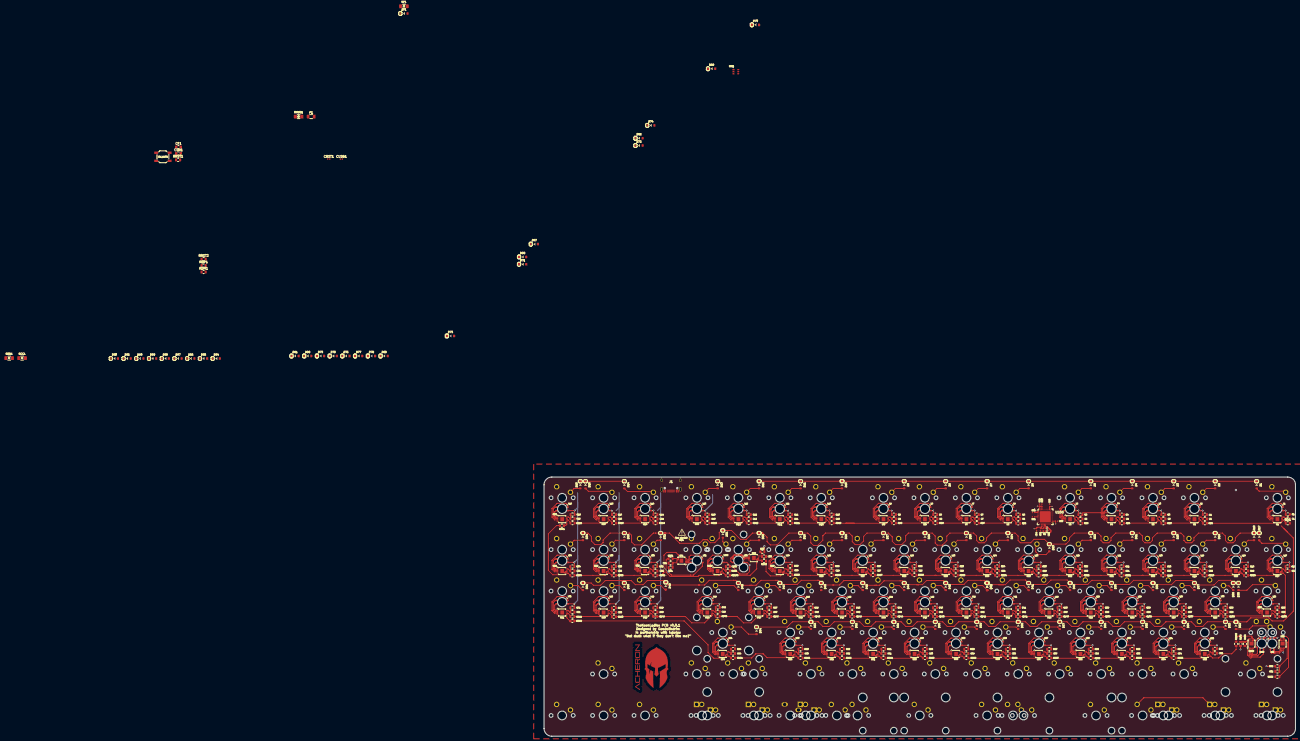
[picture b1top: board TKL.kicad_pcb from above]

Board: 2 copper layers, 345.3 x 119.1 mm, 557 parts (1 on the bottom side), 527 nets.

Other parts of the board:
D42#2: 1N4148; D_SOD-123

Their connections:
unnamed 144: D42#2.2; also elsewhere on the board
Row3: D42#2.1; also elsewhere on the board

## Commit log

2019-08-11 Placed switches
2019-08-12 Positioned switches
    - The switches were positioned onto the PCB and the first WS2811 modules and RGB LEDs also were added. As of this commit, the edge layer drawings are a simple guideline and won't reflect the final di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
    - Added plated logo
2019-08-12 Routed RGB components and reorganized columns
    - The WS2811M datasheet states that every unit must have two resistors and a capacitor around it; one resistor (33R) for the data lines and a resistor and capacitor (RC filter, 100R and 100nF) for by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
    - Laid the RGB components for some switches. Following the addition of the extra components for the RGB controllers, the RGB components (controller, resistors and capacitor and the LED) were added to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
    - The bigger 15x21mm short Acheron logo was added
2019-08-13 Further routing and placement
2019-08-13 Placed and routed second row
2019-08-15 Added third RGB row to schematic
2019-08-15 Placed RGB components L35-L51 to third row on PCB
2019-08-15 Fixed RGB and controller labels
2019-08-16 Routed 3rd row and columns
    - The RGB 3rd row was routed; all components were added, their labels fixed and cleaned.
    - All columns were routed. Some were reassigned for better fitting. It may be that I'll redo some columns in the near future as the routing does not look clean, specially in the bottom row;
    - A warning sign was added to show that, when using a screw-in stab on the 2U backspace, there should be an electric tape preventing the screw from short-circuiting to the column pad.
2019-08-16 Added TGB fourth row to schematic
2019-08-16 Placed RGB LEDs and controllers of 4th row
2019-08-16 Routed first 4 RGB LEDs
2019-08-17 Routed SW55 RGB
2019-08-17 Routed SW56 RGB LED
2019-08-17 Routed SW57 RGB LED
2019-08-17 Routed SW58 RGB LED
2019-08-17 Routed SW59 RGB LED
2019-08-17 Routed SW60 RGB LED
2019-08-17 Routed SW61 RGB LED
2019-08-17 Routed SW62 RGB LED
2019-08-17 Routed SW63 RGB LED
2019-08-17 Routed SW64 RGB LED
2019-08-17 Fix orientation of RD55, 56 and 57
2019-08-17 Renamed RD52-64 to match controller number
2019-08-17 Route fourth row
2019-08-20 Add plate DXF, route bypass capacitors
2019-08-20 Add case drawings, redo PCB edges
    - Added case drawings in Eco2.User layer
    - PCB Edges were redone to fit the case.
2019-08-20 Rotuted USB Connector and D+ D-
2019-08-20 Route connector, pre-route colummns and rows
    - The connector area was routed with the ESD and shield components. This includes USBLC6, fuse and shield discharge net.
    - The columns were routed to almost complete degree. THe were not completely routed because the bottom row may have some changes to its column ordering.
    - Columns and rows were pre-routed. This means that routes from them to the MCU were devised to indicate how they will be and to organize PCB space.
2019-08-20 - Add license and readme, update PCB backup files
    - LICENSE and README were added
    - Backup for schematic and footprint library were also modified
2019-08-21 Rename RGB 3rd row RD annotation
    - Fixed a small isue where resistors RD in the 3RD row of RGB controllers were misannotated: they were all a number ahead (i.e., where it should be RD(X) was RD(X+1))
2019-08-21 Add 4th RGB row
2019-08-21 Anntate 4th RGB LED component row
2019-08-21 Remove RGB LED 77 second instance
    - There were two instances of RGB LED 77
2019-08-21 Place 4th row of LEDs
    - The RGB LEDs of 4th row were placed. In order to do this, some traces had to be re-wired, specially the ones that link columns to their MCU pins. RGB WS2811 controllers and their respective compone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
2019-08-21 Experiment with curved traces
    - Some traces were curved
2019-08-22 Place 4th row RGB WS2811 controllers
2019-08-22 Route 5V net, columns nets
    - Routed part of the 5V net. Also routed and assgned pins to some columns and rows nets.
2019-09-01 Organized schematic
2019-09-01 Routed RGB68, 69
2019-09-01 Routed RGB70
2019-09-01 Routed RGB71
2019-09-01 Routed RGB72
2019-09-01 Routed RGB73
2019-09-01 Re-routed reset net
2019-09-01 Routed RGB74 and 75
2019-09-01 Added shield pour and keepout zone to USB area
2019-09-01 Further routed 5V trace
2019-09-01 Re-routed some columns for a cleaner routing
2019-09-01 Routed RGB76
2019-09-01 Placed last row switches
2019-09-01 Added last row RGB components to schematic
2019-09-01 Routed SW88 RGB LED
2019-09-01 Routed SW87 RGB LED
2019-09-01 Placed last row LEDs
2019-09-30 Update: routed more RGBs, removed split bottom row
2019-09-30 Update: new RGB LED footprint
    - A new footprint was used for the RGB LEDs, since the last footprint
    was noe fine adjusted and was yielding too many DRC error due to pad
    placement and hole size. See the AcheronLibrary commit 1ad4dd26 for more information.
2019-10-08 Update: Finish routing
    - All tracks were routed
    - There are some extra pins that need to be broken out.
    - Also the serial programming ISP pins need to be broken out.
    - After that is done, run DRC and correct eventual flaws
2019-10-09 Run DRC, solve issues
    - DRC was run and some issues arose. This means that some tracks needed
    to be re-routed.
    - Almost all columns and rows routed, except for Col12, Col15 and Row6.
    - The ISP JTAG pins were broken out
    - Some silkscreens were re-done for clarification
    - The shield copper fill was further distanced from the GND copper fill
2019-10-09 Route rest of cols and rows
2019-10-09 Update AcheronLib, added documentation
2019-10-09 Updated renders
2019-10-09 Added KiCad renders
2019-10-09 Update README, add KLE
2019-10-11 Rename folder 'PCB Files' to 'PCB_Files'
2019-10-13 Add RCC2, R89
    - RCC2 was added as per USB2.0 compliance;
    - R89 (pullup resistor between USB D+ and USB power) was added as per
    USB2.0 full speed devices compliance.
2019-10-13 Add choke, reset diode
    - Choke I1 and reset diode DRST1 were added for better reliability
2019-10-13 Modify ANSI version for split bottom row
2019-10-13 Deleted AcheronLibrary submodule
2019-10-13 Added AcheronLibrary updated submodule
2019-10-16 Update library, add label
    - Updated the AcheronLibrary, specifically the 6028 RGB LED footprint,
    which is now marked as an SMD component
    - The label was added
    - Renders were updated
